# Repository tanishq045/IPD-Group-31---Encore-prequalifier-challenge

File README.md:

# IPD-Group-31---Encore-prequalifier-challenge
# IPD Group 31

## Team Members

| Name                | Roll Number   | Year |
|---------------------|---------------|------|
| Tanishq Patel        | 60002220151   | TE   |
| Varun Choudhary      | 60002220220   | TE   |
| Soham Shenoy         | 60002231062   | SE   |
| Swayam Bhosale       | 60002230140   | SE   |

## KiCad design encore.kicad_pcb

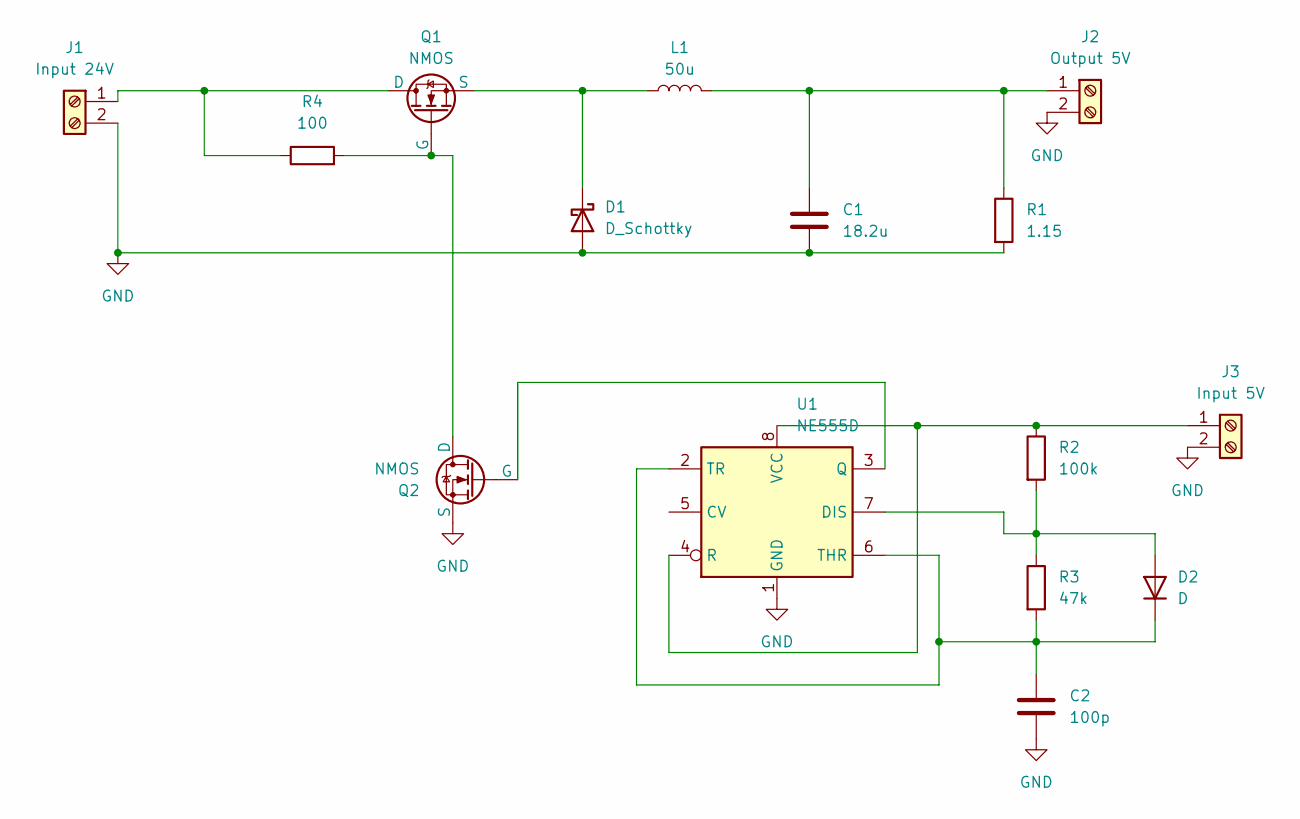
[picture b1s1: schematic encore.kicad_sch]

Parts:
C1: 18.2u; CP_Radial_D8.0mm_P3.50mm
C2: 100p; C_Disc_D3.8mm_W2.6mm_P2.50mm
D1: D_Schottky; D_DO-201AD_P12.70mm_Horizontal
D2: D; D_DO-35_SOD27_P7.62mm_Horizontal
J1: Input 24V; TerminalBlock_Phoenix_MKDS-3-2-5.08_1x02_P5.08mm_Horizontal
J2: Output 5V; TerminalBlock_Phoenix_MKDS-3-2-5.08_1x02_P5.08mm_Horizontal
J3: Input 5V; TerminalBlock_Phoenix_MKDS-3-2-5.08_1x02_P5.08mm_Horizontal
L1: 50u; L_Toroid_Vertical_L16.0mm_W8.0mm_P7.62mm
Q1, Q2: NMOS; TO-220-3_Vertical
R1: 1.15; R_Axial_DIN0207_L6.3mm_D2.5mm_P7.62mm_Horizontal
R2: 100k; R_Axial_DIN0309_L9.0mm_D3.2mm_P12.70mm_Horizontal
R3: 47k; R_Axial_DIN0309_L9.0mm_D3.2mm_P12.70mm_Horizontal
R4: 100; R_Axial_DIN0207_L6.3mm_D2.5mm_P7.62mm_Horizontal
U1: NE555D; SOIC-8_3.9x4.9mm_P1.27mm

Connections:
GND: C1.2, C2.2, D1.2 (A), J1.2, J2.2, J3.2, Q2.3 (S), R1.2, U1.1 (GND)
unnamed: D1.1 (K), L1.1, Q1.3 (S)
unnamed: D2.2 (A), R2.2, R3.1, U1.7 (DIS)
unnamed: C2.1, D2.1 (K), R3.2, U1.2 (TR), U1.6 (THR)
unnamed: J1.1, Q1.1 (D), R4.1
unnamed: C1.1, J2.1, L1.2, R1.1
unnamed: J3.1, R2.1, U1.4 (R), U1.8 (VCC)
unnamed: Q1.2 (G), Q2.1 (D), R4.2
unnamed: Q2.2 (G), U1.3 (Q)

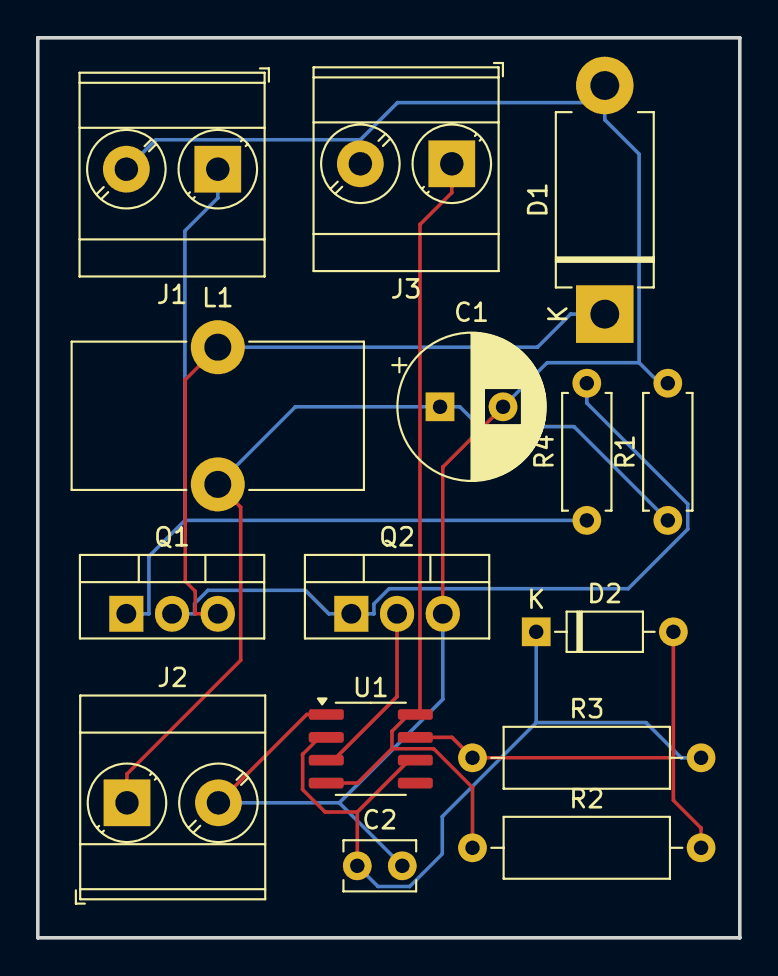
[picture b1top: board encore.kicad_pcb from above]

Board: 2 copper layers, 39.0 x 50.0 mm, 15 parts (0 on the bottom side), 9 nets.

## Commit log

2024-09-26 README.md
